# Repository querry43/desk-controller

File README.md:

Desk Controller
===============

Specifications
--------------
 * 29V 3A supply
 * Direction control
 * PWM speed control

Component List
--------------
* 1x EC2-5NU
* 1x FQP30N06L
* 2x 1k resistor
* 1x 10k resistor
* 1x 2n3904
* 1x 1N4148
* 2x 2-pin 3.5mm pitch screw terminals
* 1x 4-pin 0.1" pitch straight headers

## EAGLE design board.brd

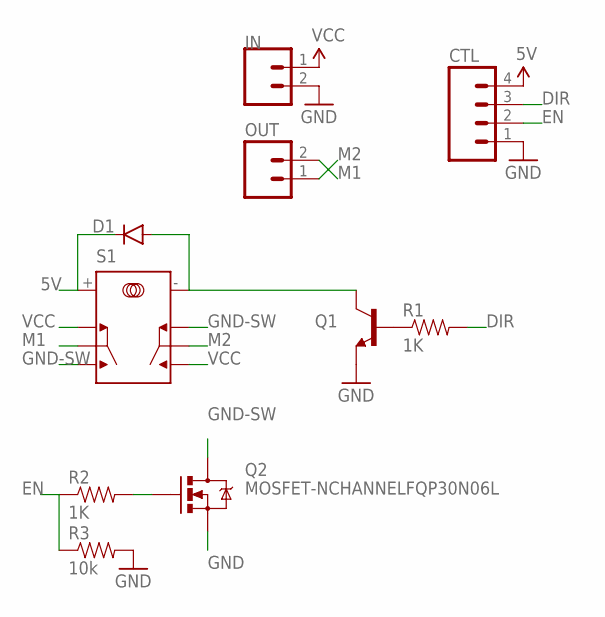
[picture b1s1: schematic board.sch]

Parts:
CTL: M041X04_NO_SILK; 1X04_NO_SILK
D1: DIODE1N4148; DIODE-1N4148
IN: M023.5MM; SCREWTERMINAL-3.5MM-2
OUT: M023.5MM; SCREWTERMINAL-3.5MM-2
Q1: TRANSISTOR_NPNTO-92-AMMO; TO-92-AMMO
Q2: MOSFET-NCHANNELFQP30N06L; TO220V
R1, R2: 1K; AXIAL-0.3
R3: 10k; AXIAL-0.3
S1: EC2-5NU

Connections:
5V: CTL.4, D1.C, S1.+
$1: D1.A, Q1.3 (C), S1.-
DIR: CTL.3, R1.P$2 (2)
EN: CTL.2, R2.P$1 (1), R3.P$1 (1)
GND: CTL.1, IN.2, Q1.1 (E), Q2.3 (S), R3.P$2 (2)
GND-SW: Q2.2 (D), S1.NC2, S1.NO1
M1: OUT.2, S1.COM1
M2: OUT.1, S1.COM2
unnamed: Q2.1 (G), R2.P$2 (2)
unnamed: Q1.2 (B), R1.P$1 (1)
VCC: IN.1, S1.NC1, S1.NO2

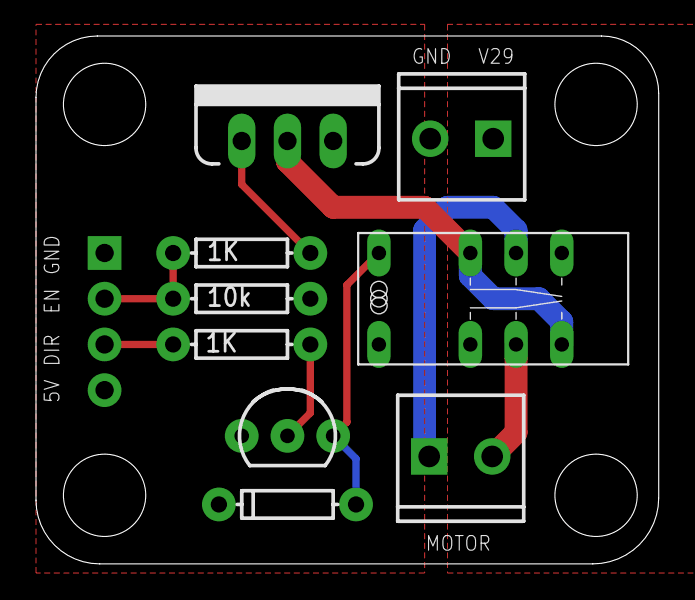
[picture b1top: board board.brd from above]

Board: 2 copper layers, 34.6 x 29.3 mm, 10 parts (0 on the bottom side), 11 nets.

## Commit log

2017-06-24 :lollipop: Added .gitattributes & .gitignore files
2017-06-24 adding readme and license

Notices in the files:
parts and their libraries:
SparkFun-DiscreteSemi: Licensing: Creative Commons ShareAlike 4.0 International - https://creativecommons.org/licenses/by-sa/4.0
